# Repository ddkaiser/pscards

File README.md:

# pscards
Custom cards for restoring or repairing Korg PS-3x00 polyphonic synthesizers

## Overview

### Goal
Korg Polyphonic Synthesizers (PS-3100, PS-3200, PS-3300) are complex and expensive synthesizers, but as these instruments are now at least 45 years old, occasionally their original parts fail, and there is a need for recreated parts, in order to keep the instrument in operating condition.

This project is to create spare circuit boards to keep these old synthesizers operating.

### Sub-Projects
- [`KLM-69`](KLM-69) : KiCad project
	-	KLM - 69 "GATE" board
		-	PS-3100 has KLM-69E
		-	PS-3200 has KLMC-69F or KLM-69G  (are these identical, unknown revision?)
- [`KLM-64`](KLM-64) : KiCad project
	-	KLM - 64 "SIGNAL GENERATOR" board
		-	PS-3100 has KLM-64E
		-	PS-3200 has KLMC-064D  (are these identical, unknown revision?)
- [`card-extender`](card-extender) : KiCad project
	-	Diagnostic support board
		-	A pass-through board that extends a card outside the Korg synth chassis, to enable easier access while diagnosing and repairing
		-	Plugs-in to Korg synth backplane, and provides 2 44-pin card socket connections to host the Korg KLM board.
		-	Sockets can be: [Sullins EBM22DREH](https://www.sullinscorp.com/product/?pn=EBM22DREH), [EDAC 305-044-520-202](https://edac.net/series/305?search_part=305-044-520-202), [Vector R644](https://www.vectorelect.com/connector-card-edge.html) or similar card sockets.
		-	Provides test-points in Molex 0.156” (3.96mm) header format, using vertical headers, [Molex KK396 part #0026481240](https://www.molex.com/en-us/products/part-detail/26481240)
- [`klib`](klib) : “KiCad Libraries” folder
	-	KiCad shared libraries (symbols, footprints, images, drawing sheets, project templates, 3D models) to be used common across sub-projects
	-	Shared folder should be referenced in sub-projects as `${KIPRJMOD}/../klib/`

## Criteria

### Technical Requirements
Original boards are:
- single-sided:
  - top layer has silk-screen component labels but no traces or soldermask
  - bottom layer of board has copper traces and soldermask
- 1.6mm thickness PCB
- 1oz. copper plating
	
#### Dimensions
- Dimensioning of card assumes landscape orientation
- Height: 177mm  (including edge-connector).
- Width: 240mm
- Edge connector pads mirror card-edge traces, but there can be some variance in edge connector sizing & placing
	- Edge connectors can be between 87.5mm & 89mm in width and 10mm in height.
	- Edge connectors can be from 14mm to 15.5mm from outer (left/right) card edge.
	- Edge connectors can have a 32.5mm to 34mm gap between them.

### Design Requirements
- Circuit projects require KiCad 8.0+
- Schematics pages are A4-sized
- Dimensioning in millimeters (mm)

## Notes

### External Resources
- Korg PS-3100 Schematic PDF document was retrieved from: https://archive.org/details/synthmanual-korg-ps-3100-schematics/

### Original Work is by Korg
- All references to the word Korg, pcb names and numbers, (KLM*) or use of Korg component references or other design, are based on the original work by Korg.
- This work in this project is to repair and restore an original Korg synthesizer, based on its service documents and schematics.

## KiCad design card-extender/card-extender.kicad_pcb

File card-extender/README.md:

# pscards/card-extender

## Overview
KiCad project for creating a extender card. The extender card is useful for working on a Korg PS-Series Polyphonic Synthesizer.

The card is a pass-through board that extends a card outside the Korg synth chassis, to enable easier access while diagnosing and repairing

The extender card plugs-in to Korg synth backplane, and provides 2 44-pin card socket connections to host the Korg KLM board.

## Parts

### Card-Edge Sockets
Sockets can be:

-	[Sullins EBM22DREH](https://www.sullinscorp.com/product/?pn=EBM22DREH)
-	[EDAC 305-044-520-202](https://edac.net/series/305?search_part=305-044-520-202)
-	[Vector R644](https://www.vectorelect.com/connector-card-edge.html)
-	or similar card sockets.

### Test Points
The card provides header pads for adding test points. 

The test points are:
-	Molex 0.156” (3.96mm) header format, using vertical headers
-	[Molex KK396 part #0026481240](https://www.molex.com/en-us/products/part-detail/26481240)

### Card Dimensions
- Dimensioning of card assumes landscape orientation
- Height: 228mm  (including edge-connector).
- Width: 240mm
- Edge connector pads mirror card-edge traces, but there can be some variance in edge connector sizing & placing
	- Edge connectors can be between 87.5mm & 89mm in width and 10mm in height.
	- Edge connectors can be from 14mm to 15.5mm from outer (left/right) card edge.
	- Edge connectors can have a 32.5mm to 34mm gap between them.

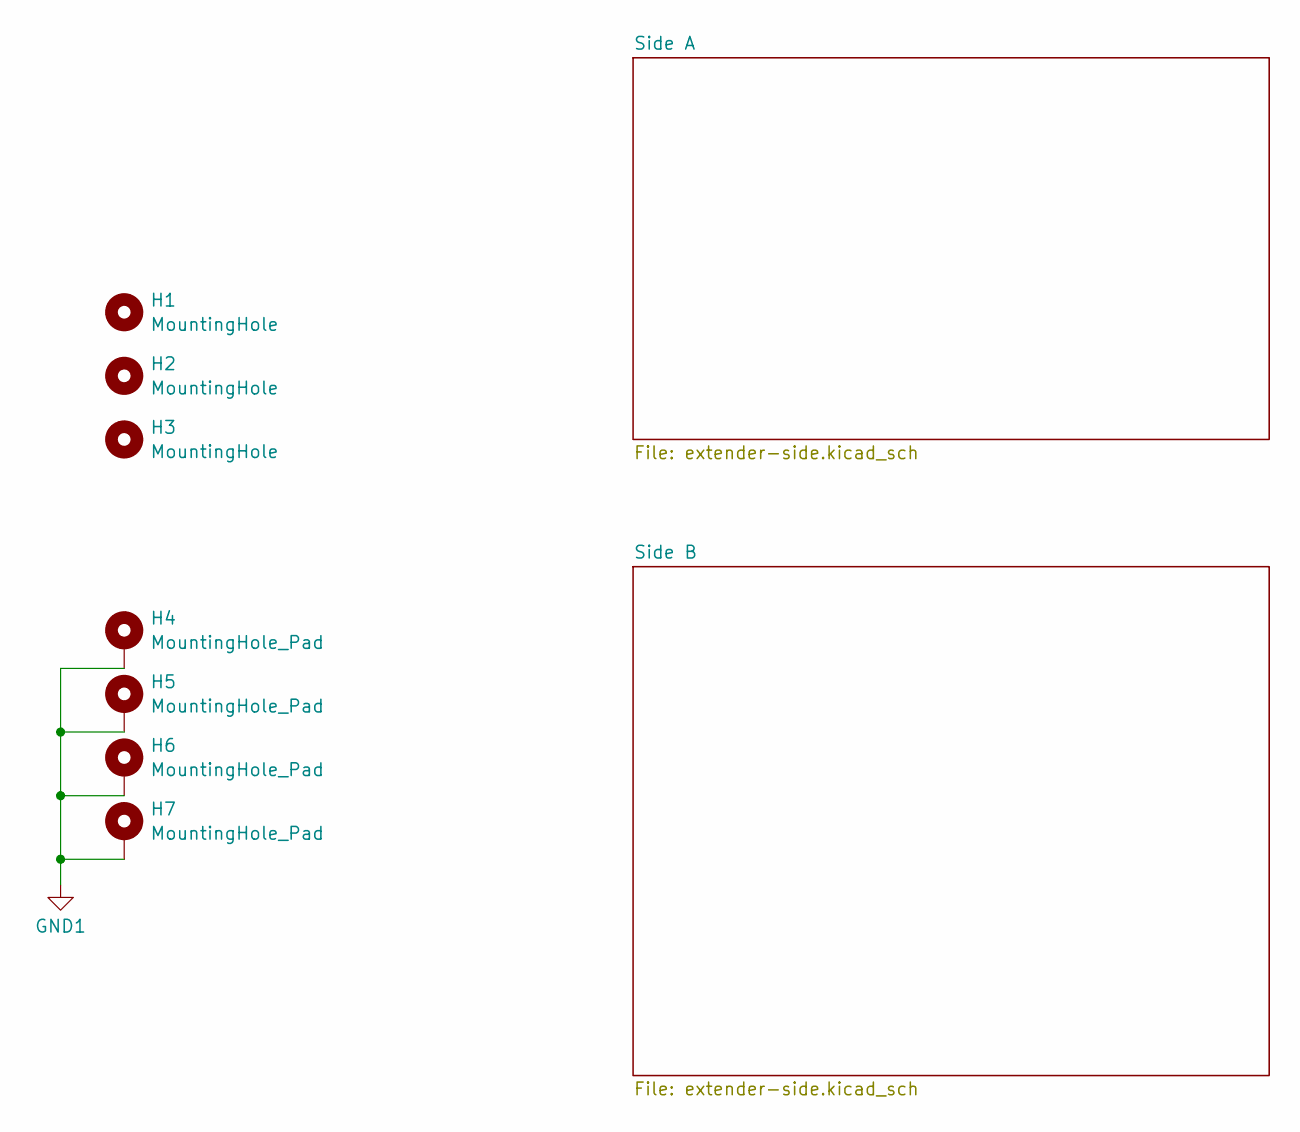
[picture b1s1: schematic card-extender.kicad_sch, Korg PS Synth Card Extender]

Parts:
H1, H2, H3: MountingHole; MountingHole_2.5mm
H4, H5, H6, H7: MountingHole_Pad; MountingHole_2.2mm_M2_Pad

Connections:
GND1: H4.1, H5.1, H6.1, H7.1

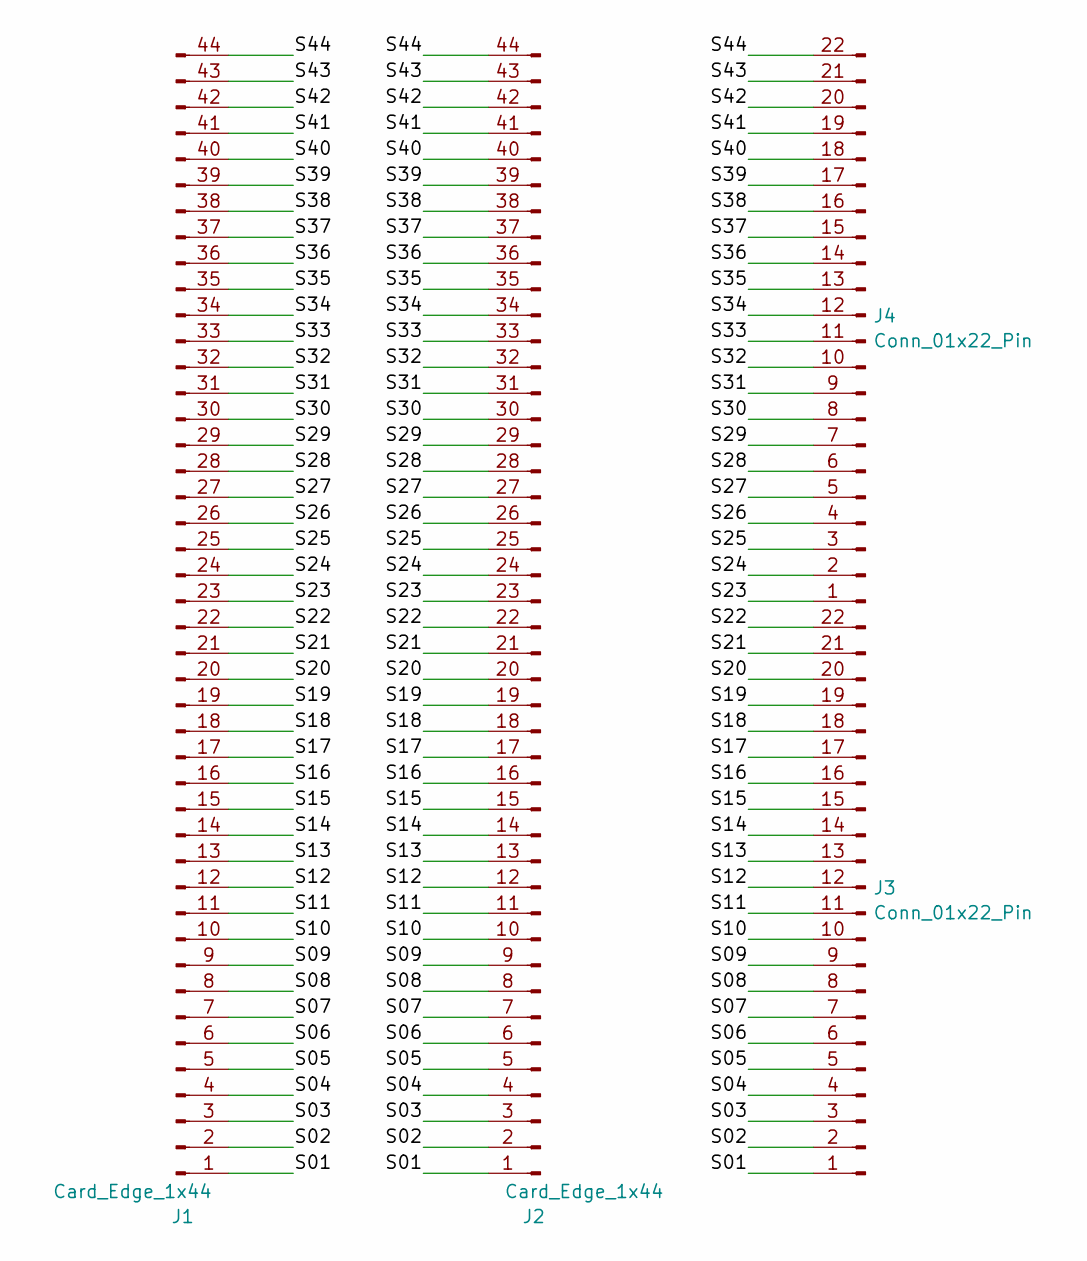
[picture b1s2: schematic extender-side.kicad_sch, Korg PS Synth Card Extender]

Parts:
J1, J2: Card_Edge_1x44; CardEdge-2x22_2.18x9.75mm_P3.96mm
J3, J4: Conn_01x22_Pin; Molex_KK-396_A-41791-0022_1x22_P3.96mm_Vertical

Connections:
/Side A/S01: J1.1, J2.1, J3.1
/Side A/S02: J1.2, J2.2, J3.2
/Side A/S03: J1.3, J2.3, J3.3
/Side A/S04: J1.4, J2.4, J3.4
/Side A/S05: J1.5, J2.5, J3.5
/Side A/S06: J1.6, J2.6, J3.6
/Side A/S07: J1.7, J2.7, J3.7
/Side A/S08: J1.8, J2.8, J3.8
/Side A/S09: J1.9, J2.9, J3.9
/Side A/S10: J1.10, J2.10, J3.10
/Side A/S11: J1.11, J2.11, J3.11
/Side A/S12: J1.12, J2.12, J3.12
/Side A/S13: J1.13, J2.13, J3.13
/Side A/S14: J1.14, J2.14, J3.14
/Side A/S15: J1.15, J2.15, J3.15
/Side A/S16: J1.16, J2.16, J3.16
/Side A/S17: J1.17, J2.17, J3.17
/Side A/S18: J1.18, J2.18, J3.18
/Side A/S19: J1.19, J2.19, J3.19
/Side A/S20: J1.20, J2.20, J3.20
/Side A/S21: J1.21, J2.21, J3.21
/Side A/S22: J1.22, J2.22, J3.22
/Side A/S23: J1.23, J2.23, J4.1
/Side A/S24: J1.24, J2.24, J4.2
/Side A/S25: J1.25, J2.25, J4.3
/Side A/S26: J1.26, J2.26, J4.4
/Side A/S27: J1.27, J2.27, J4.5
/Side A/S28: J1.28, J2.28, J4.6
/Side A/S29: J1.29, J2.29, J4.7
/Side A/S30: J1.30, J2.30, J4.8
/Side A/S31: J1.31, J2.31, J4.9
/Side A/S32: J1.32, J2.32, J4.10
/Side A/S33: J1.33, J2.33, J4.11
/Side A/S34: J1.34, J2.34, J4.12
/Side A/S35: J1.35, J2.35, J4.13
/Side A/S36: J1.36, J2.36, J4.14
/Side A/S37: J1.37, J2.37, J4.15
/Side A/S38: J1.38, J2.38, J4.16
/Side A/S39: J1.39, J2.39, J4.17
/Side A/S40: J1.40, J2.40, J4.18
/Side A/S41: J1.41, J2.41, J4.19
/Side A/S42: J1.42, J2.42, J4.20
/Side A/S43: J1.43, J2.43, J4.21
/Side A/S44: J1.44, J2.44, J4.22

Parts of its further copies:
J5, J6: Card_Edge_1x44; CardEdge-2x22_2.18x9.75mm_P3.96mm
J7, J8: Conn_01x22_Pin; Molex_KK-396_A-41791-0022_1x22_P3.96mm_Vertical

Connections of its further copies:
/Side B/S01: J5.1, J6.1, J7.1
/Side B/S02: J5.2, J6.2, J7.2
/Side B/S03: J5.3, J6.3, J7.3
/Side B/S04: J5.4, J6.4, J7.4
/Side B/S05: J5.5, J6.5, J7.5
/Side B/S06: J5.6, J6.6, J7.6
/Side B/S07: J5.7, J6.7, J7.7
/Side B/S08: J5.8, J6.8, J7.8
/Side B/S09: J5.9, J6.9, J7.9
/Side B/S10: J5.10, J6.10, J7.10
/Side B/S11: J5.11, J6.11, J7.11
/Side B/S12: J5.12, J6.12, J7.12
/Side B/S13: J5.13, J6.13, J7.13
/Side B/S14: J5.14, J6.14, J7.14
/Side B/S15: J5.15, J6.15, J7.15
/Side B/S16: J5.16, J6.16, J7.16
/Side B/S17: J5.17, J6.17, J7.17
/Side B/S18: J5.18, J6.18, J7.18
/Side B/S19: J5.19, J6.19, J7.19
/Side B/S20: J5.20, J6.20, J7.20
/Side B/S21: J5.21, J6.21, J7.21
/Side B/S22: J5.22, J6.22, J7.22
/Side B/S23: J5.23, J6.23, J8.1
/Side B/S24: J5.24, J6.24, J8.2
/Side B/S25: J5.25, J6.25, J8.3
/Side B/S26: J5.26, J6.26, J8.4
/Side B/S27: J5.27, J6.27, J8.5
/Side B/S28: J5.28, J6.28, J8.6
/Side B/S29: J5.29, J6.29, J8.7
/Side B/S30: J5.30, J6.30, J8.8
/Side B/S31: J5.31, J6.31, J8.9
/Side B/S32: J5.32, J6.32, J8.10
/Side B/S33: J5.33, J6.33, J8.11
/Side B/S34: J5.34, J6.34, J8.12
/Side B/S35: J5.35, J6.35, J8.13
/Side B/S36: J5.36, J6.36, J8.14
/Side B/S37: J5.37, J6.37, J8.15
/Side B/S38: J5.38, J6.38, J8.16
/Side B/S39: J5.39, J6.39, J8.17
/Side B/S40: J5.40, J6.40, J8.18
/Side B/S41: J5.41, J6.41, J8.19
/Side B/S42: J5.42, J6.42, J8.20
/Side B/S43: J5.43, J6.43, J8.21
/Side B/S44: J5.44, J6.44, J8.22

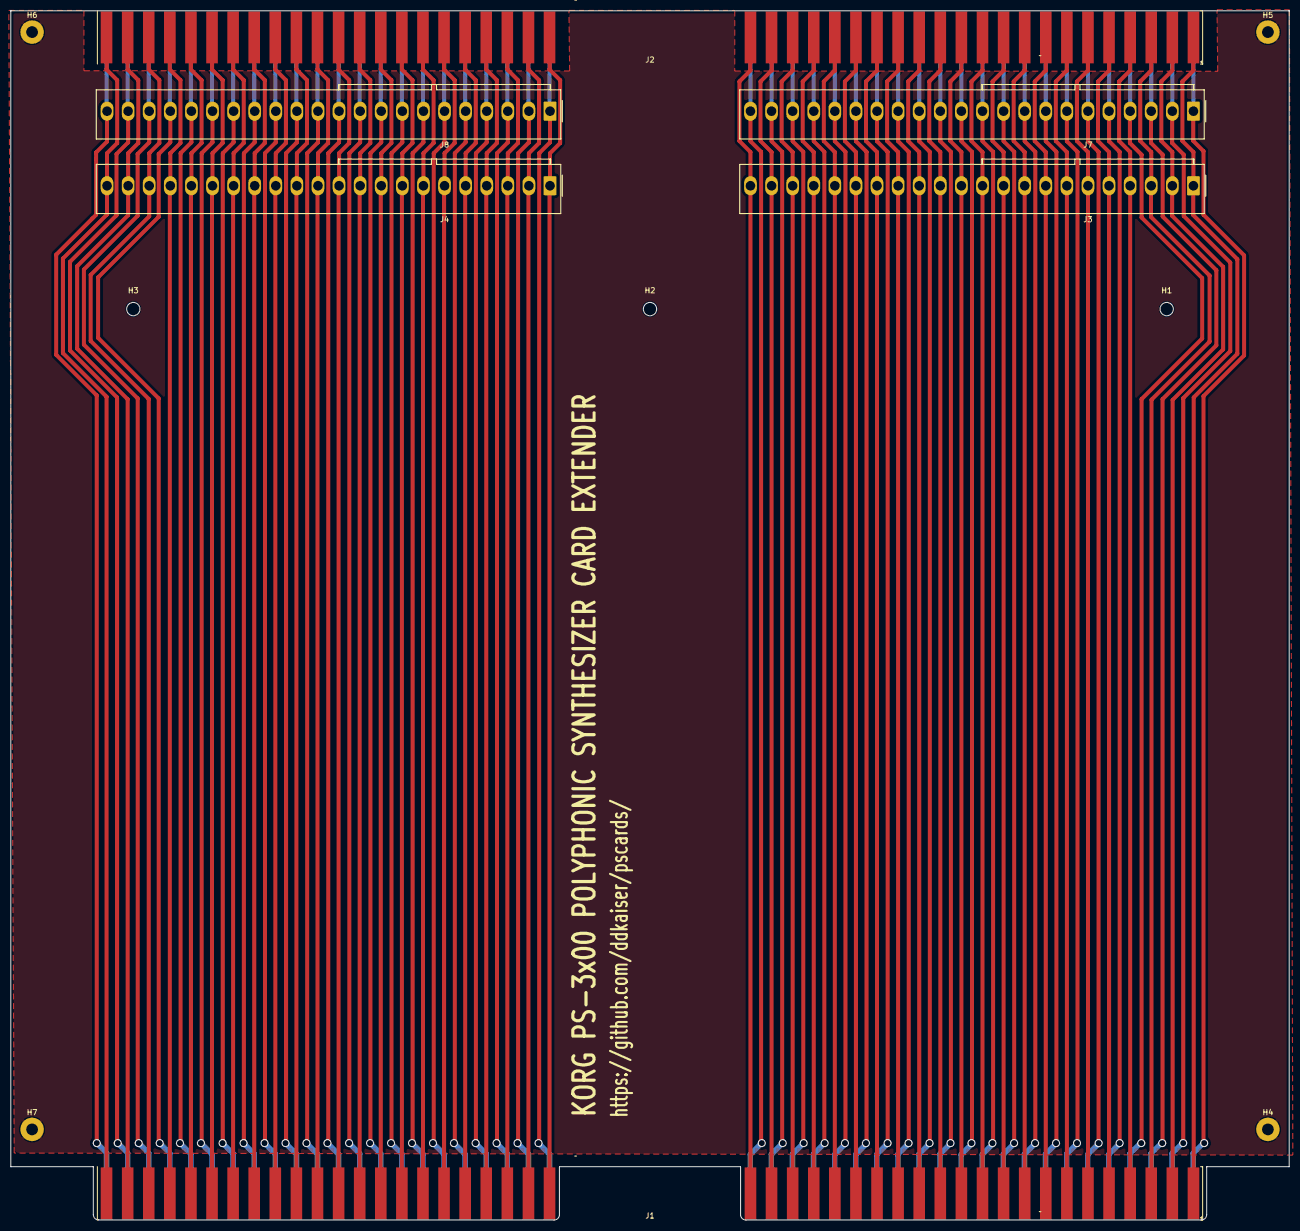
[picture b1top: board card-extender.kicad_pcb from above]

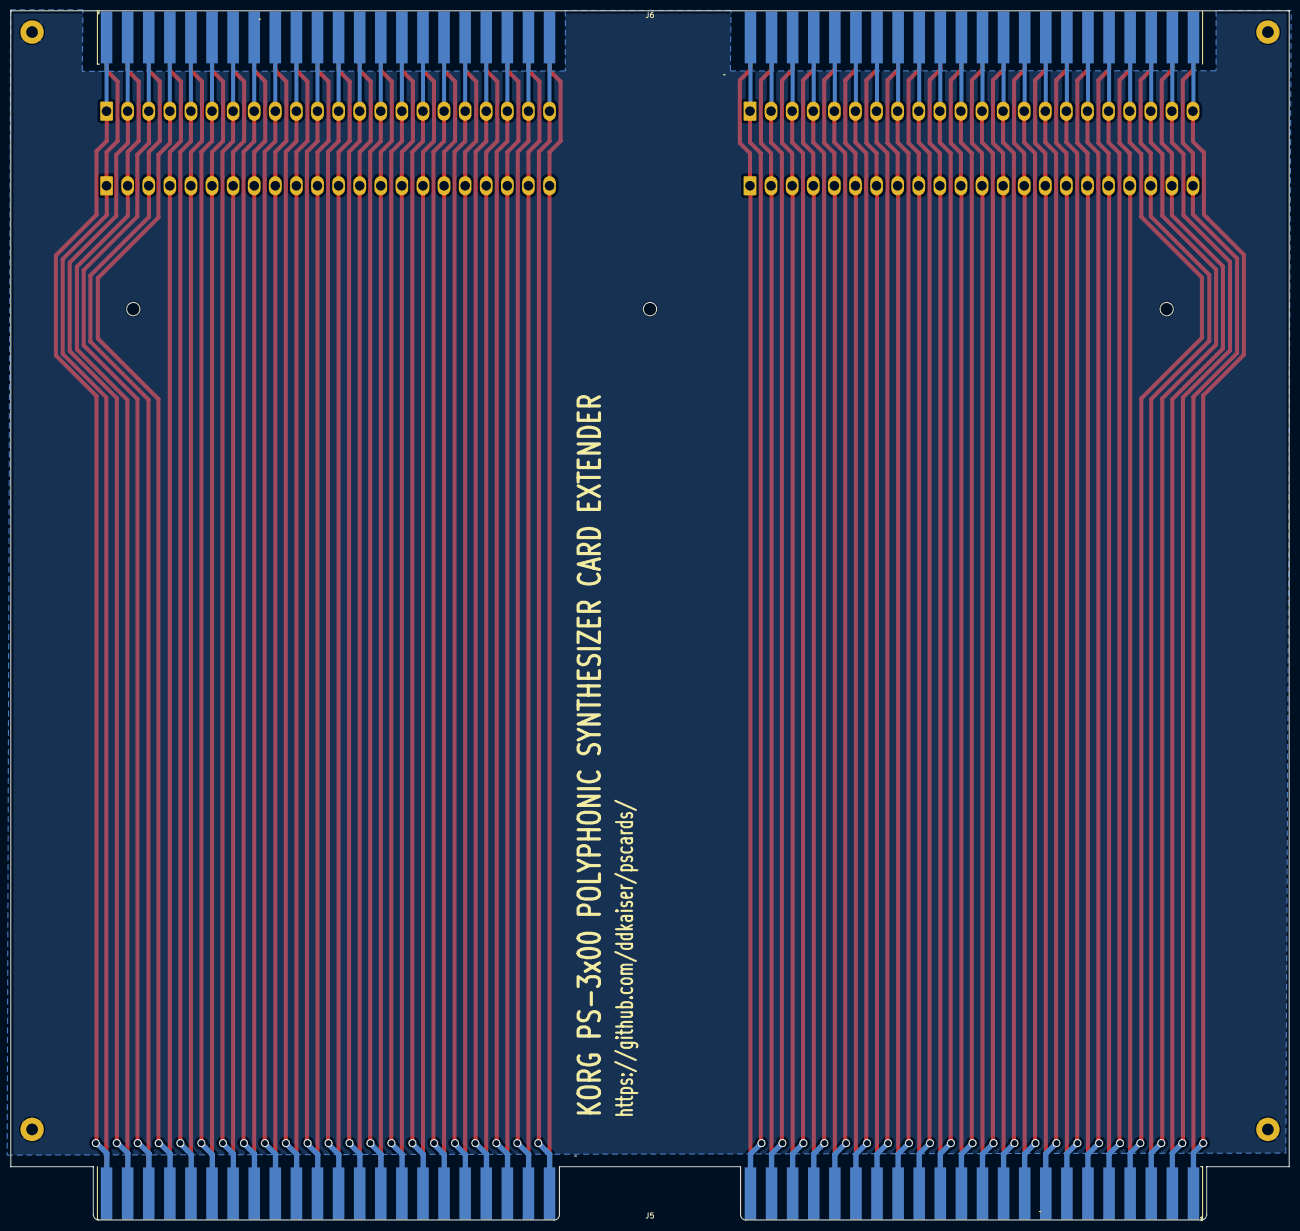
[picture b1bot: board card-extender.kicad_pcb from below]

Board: 2 copper layers, 240.0 x 227.0 mm, 15 parts (2 on the bottom side), 89 nets.

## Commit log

2024-07-19 added dimensions for cards
2024-07-20 changed orientation to landscape
2024-07-22 added card-extender
2024-07-22 Starter, template project with empty card
2024-07-23 moving footprint to project library
2024-07-23 adding 3d model for socket connector
2024-07-23 adding attribution fields
2024-07-23 adjusting documentation links and sizing
